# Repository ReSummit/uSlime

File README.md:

<div></div>

Micro form of SlimeVR trackers using BNO085 and ESP32-C6-MINI module, as small as possible

Limited to 1 sided PCB but utilizes two layer to achieve a maximal dimension of 25mm x 28mm (including the ESP32-C6-MINI module)

Also includes some test points if you wanna add idk RGB lights to it or something like that lol

## PCB Variants and Versions

Currently, v1.0.0 is the preferred PCB version and is listed in the releases. As a note, your red charge LED will always be on while the device is on. While this makes for a good indicator that your tracker is on, some may not like that the LED is always on. v1.1.0 fixes this but results in a long trace, change in pinout, and additional components needed.

**If you do not mind the always on LED, use v1.0.0 as it is less likely to result in RF issues. If you are bothered by the LED, use a 2k or higher SMD resistor value or use v1.1.0.**

On variants, there are currently three different types of main board PCBs and 2 types of supplementary modules. The first kind are listed as follows:
* uSlime_PCB: The default PCB with the BNO085 circuit on board. Contains the working BNO085 utilizing the internal crystal (of which there is little room for an external crystal)
* uSlime_PCB_Module: Similar to the default PCB; however, the BNO085 is replaced with a 5 pin I2C pin for attaching a uSlime_BNO085_Module on the back or front side of the PCB (in case you want to replace the IMU with a better one).
* uSlime_PCB_Pack: The default PCB but using pack resistors to attempt the reduction of part placements by quantity. **This has not been updated to v1.0.0 yet, DO NOT USE.**

For supplementary modules, the variants are as follows:
* uSlime_BNO085_Module: The default PCB for supplementary modules. In addition to the connectors that are compatible with the original SlimeVR trackers, they also have headers that you can use to connect it to something else instead if you decide not to use it for SlimeVR. This increases the versatility of the IMU for other projects. Due to the small size, a crystal could not be placed; however, one could be placed with a slightly larger PCB size.
* uSlime_BNO085: The other PCB for supplementary modules without the header pins. This is if you are sure that you are only using this for SlimeVR. You can technically still use this for other projects like with headers, but you will likely solder on wires.

## BOM and Pre-requisites

Bill of materials (BOMs) can be found in the `bom` folder within the respective PCB folder. These are generated on a by release basis, so they may not be up to date. It is highly recommended to generate the BOM using the "`Interactive Html Bom`" plugin found in typical KiCAD repository plugins.  
**Following the BOM placements using a BOM plugin to show where components are placed is mandatory, as there is no space for reference designators on the PCB.**

In addition to this, a hot plate, solder paste, and some needle tipped tweezers are also required. Flux may also be needed to fix any bridges that pop up on the board. Obviously, the components on the BOM are also required.

## Building the PCB

When ordering the PCB, choose to place the JLC PCB indicator as a preferred spot is placed on the PCB itself (if using JLCPCB for PCB production). You should also get a stencil to put solder paste on the PCB.

**Again, following the BOM placements using a BOM plugin to show where components are placed is mandatory, as there is no space for reference designators on the PCB.**
Place solder paste on the PCB. Afterwards, follow the Interactive HTML BOM to place all the capacitors, resistors, IMU, and MCU on the PCB. When ready, you can then place this on a hot plate. Please make sure that there are no bridges on the BNO085 or the USB C connector, as these can cause issues with functionality.

## Verification (MUST READ)

<div><center>   

**Before testing and using, make sure to bridge the address bridge pads on the back of the PCB.** Verify that the board and the IMU functions by flashing the ESP32-C6 firmware first. If there is no address response, something may be wrong with the IMU (more likely to fail). Once you have verified that the IMU and MCU works, you can then solder the rest of the THT components such as the external IMU connector and battery connector.

## Firmware

The PCB currently uses a ESP32-C6 or equivalent MCU. Right now, there is a pull request to introduce this MCU into the SlimeVR ESP32 firmware located here:  
[SlimeVR ESP32-C6 Pull Request](https://github.com/SlimeVR/SlimeVR-Tracker-ESP/pull/327)

The Arduino core is technically updated but is still pending its full support to the ESP32-C6 line. Therefore, treat this as a beta firmware and subject to broken features or bugs.

## PCB Limitations

Due to the inherent nature of this PCB, there is a chance that this PCB may produce RF. We have not tested for RF emission but regardless, be careful if using this in RF restricted environments.

Also, the main PCB does not have USB voltage protection circuits! Unfortunately, we ran out of time for the release but it is plausible to add it...

In addition, due to the single-sided PCB layout, this is not technically as small as it could be. There have been countless videos that showcase the design possibly being smaller. Some resistor and SMD components can also be moved to the back due to the ease in soldering those components. However, those are slated for a v2.0.0 PCB and is not expected to be released within anytime this year.

Lastly, it is known that the charger SMD compoenent tends to heat up rather quickly while charging the battery. This shouldn't reach the melting point of solder but it is worth mentioning; perhaps a more efficient IC would be better here.

## Images:
<div></div>

## Footprints Used

Some footprints and symbols were used from other sources:
* ESP32-C6 Symbol: https://github.com/sparkfun/SparkFun_Thing_Plus_ESP32_C6
* ESP32-C6 Footprint: https://github.com/espressif/kicad-libraries
* BNO085 Footprint: Provided by Colin
* AP2112K-3.3TRG1 and MCP73831T-2ACI/OT Symbol / Footprint: From a class project :)
* MHT150RGBCT Footprint: Converted from EasyEDA
* JST ZH Pinout: Same as SlimeVR PCB :D

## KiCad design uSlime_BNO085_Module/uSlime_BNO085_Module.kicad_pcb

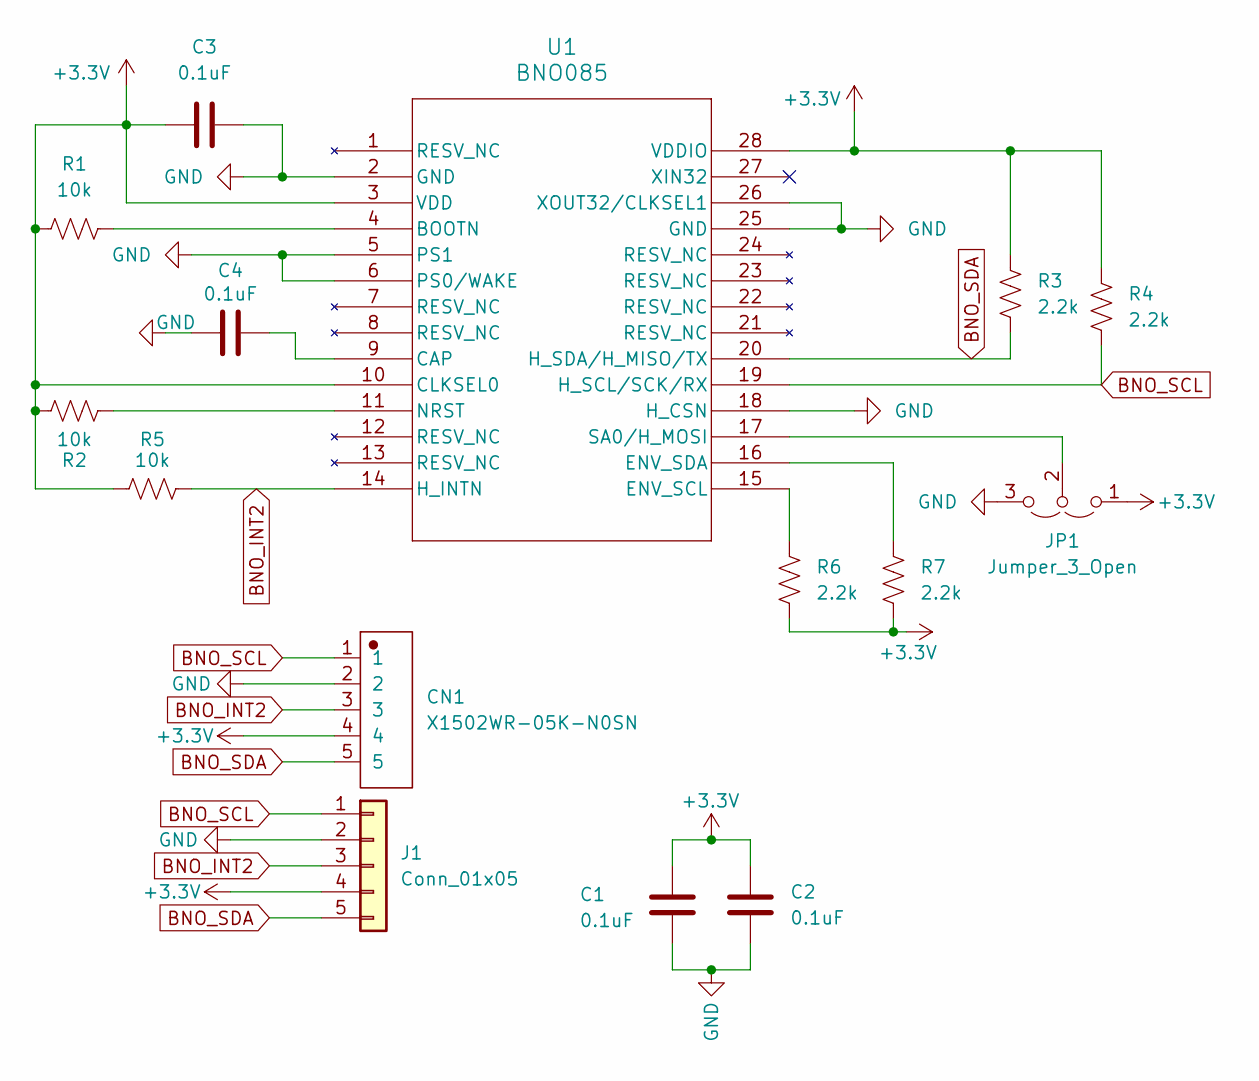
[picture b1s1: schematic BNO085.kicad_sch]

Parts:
C1, C2, C3, C4: 0.1uF; C_0402_1005Metric
CN1: X1502WR-05K-N0SN; CONN-TH_5P-P1.50_X1502WR-05K-N0SN
J1: Conn_01x05; PinHeader_1x05_P2.54mm_Vertical
JP1: Jumper_3_Open; SolderJumper-3_P1.3mm_Open_RoundedPad1.0x1.5mm
R1, R2, R5: 10k; R_0402_1005Metric
R3, R4, R6, R7: 2.2k; R_0402_1005Metric
U1: BNO085; BNO080

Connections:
+3.3V: C1.2, C2.2, C3.1, CN1.4, J1.4, JP1.1 (A), R1.1, R2.2, R3.1, R4.1, R5.1, R6.2, R7.2, U1.3 (VDD), U1.10 (CLKSEL0), U1.28 (VDDIO)
BNO_INT2: CN1.3, J1.3, R5.2, U1.14 (H_INTN)
BNO_SCL: CN1.1, J1.1, R4.2, U1.19 (H_SCL/SCK/RX)
BNO_SDA: CN1.5, J1.5, R3.2, U1.20 (H_SDA/H_MISO/TX)
GND: C1.1, C2.1, C3.2, C4.1, CN1.2, J1.2, JP1.3 (B), U1.2 (GND), U1.5 (PS1), U1.6 (PS0/WAKE), U1.18 (H_CSN), U1.25 (GND), U1.26 (XOUT32/CLKSEL1)
unnamed: JP1.2 (C), U1.17 (SA0/H_MOSI)
unnamed: R1.2, U1.4 (BOOTN)
unnamed: C4.2, U1.9 (CAP)
unnamed: R6.1, U1.15 (ENV_SCL)
unnamed: R7.1, U1.16 (ENV_SDA)
unnamed: R2.1, U1.11 (NRST)

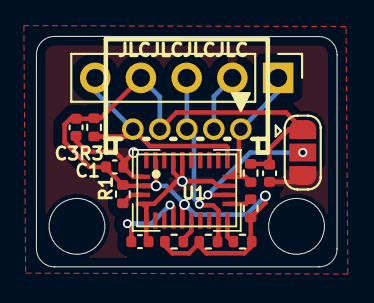
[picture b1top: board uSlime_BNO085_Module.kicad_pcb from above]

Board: 2 copper layers, 16.7 x 12.8 mm, 15 parts (0 on the bottom side), 11 nets.

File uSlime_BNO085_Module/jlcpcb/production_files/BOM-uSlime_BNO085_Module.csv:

Comment,Designator,Footprint,LCSC,Quantity
0.1uF,"C1,C2,C3,C4",C_0402_1005Metric,C141382,4
10k,"R1,R2,R5",R_0402_1005Metric,C25744,3
2.2k,"R3,R4,R6,R7",R_0402_1005Metric,C25879,4
X1502WR-05K-N0SN,CN1,CONN-TH_5P-P1.50_X1502WR-05K-N0SN,C561537,1
Conn_01x05,J1,PinHeader_1x05_P2.54mm_Vertical,,1
BNO085,U1,BNO080,,1

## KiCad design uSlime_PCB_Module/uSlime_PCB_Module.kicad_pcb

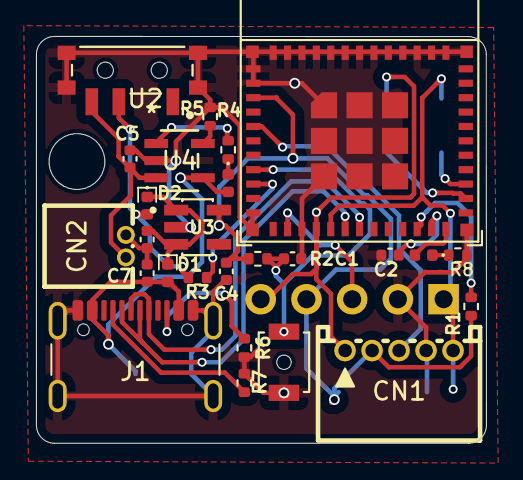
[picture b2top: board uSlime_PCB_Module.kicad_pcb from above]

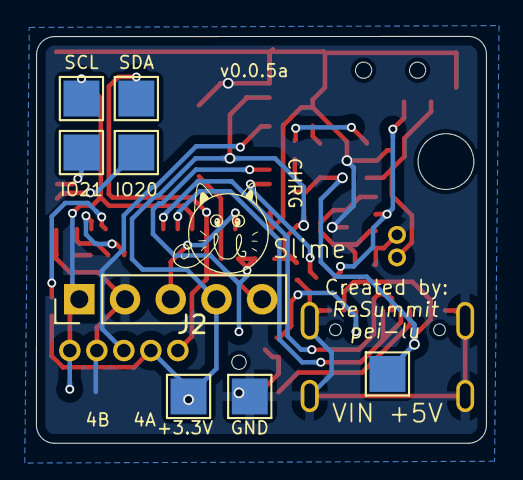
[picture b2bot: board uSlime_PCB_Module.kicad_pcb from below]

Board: 2 copper layers, 25.0 x 22.6 mm, 34 parts (8 on the bottom side), 25 nets.

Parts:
C1, C2: 0.1uF; C_0402_1005Metric
C3, C4: 10uF; C_0402_1005Metric
C5, C7: 10μF; C_0402_1005Metric
CHRG1: LED; LED_0402_1005Metric
CN1: X1502WR-05K-N0SN; CONN-TH_5P-P1.50_X1502WR-05K-N0SN
CN2: 1.25T-2AW; CONN-TH_2P-P1.25_1.25T-2AW
D1, D2: D; D_0402_1005Metric
J1: USB_C_Receptacle_USB2.0_14P; USB_C_Receptacle_GCT_USB4105-xx-A_16P_TopMnt_Horizontal
J2: Conn_01x05; PinHeader_1x05_P2.54mm_Vertical
R1, R2: 100k; R_0402_1005Metric
R3: 180k; R_0402_1005Metric
R4, R8: 1k; R_0402_1005Metric
R5: 2k; R_0402_1005Metric
R6, R7: 5.1k; R_0402_1005Metric
RESET1: SW_Push; SW_SPST_B3U-1000P-B
STAT1: LED; LED_0402_1005Metric
TP1: SDA; TestPoint_Pad_2.0x2.0mm
TP2: SCL; TestPoint_Pad_2.0x2.0mm
TP3, TP4: IO14; TestPoint_Pad_2.0x2.0mm
TP5: 3.3V; TestPoint_Pad_2.0x2.0mm
TP6: GND; TestPoint_Pad_2.0x2.0mm
TP7: VBUS; TestPoint_Pad_2.0x2.0mm
U1: ESP32-C6-MINI-1
U2: MSK-12C02_SMD_SPDT_SWITCH; SW_PCM12SMTR
U3: AP2112K-3.3TRG1; SOT95P285X140-5N
U4: MCP73831T-2ACI/OT; SOT-23-5_MC_MCH

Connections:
+3.3V: C4.1, CN1.2, J2.4, R1.2, R2.2, TP5.1, U1.3 (3V3), U3.5 (VOUT)
/ESP32-C6FH4/ESP_EN: C1.1, R2.1, RESET1.2, U1.8 (EN)
/ESP32-C6FH4/IO8: R1.1, U1.22 (IO8)
/ESP32-C6FH4/IO9/BOOT: C2.1, U1.23 (IO9)
/ESP32-C6FH4/IO18/~CS: STAT1.2 (A), U1.24 (SDIO_CMD/IO18)
/ESP32-C6FH4/IO20/PICO: TP3.1, U1.26 (SDIO_D0/IO20)
/ESP32-C6FH4/IO21/POCI: TP4.1, U1.27 (SDIO_D1/IO21)
BNO_INT: J2.3, U1.13 (XTAL_32K_N/IO1)
BNO_INT2: CN1.3, U1.5 (IO2)
BNO_SCL: CN1.5, J2.1, TP2.1, U1.16 (MTDO/LP_SCL/IO7)
BNO_SDA: CN1.1, J2.5, TP1.1, U1.15 (MTCK/LP_SDA/IO6)
BatSense: R3.2, U1.9 (MTMS/LP_RX/IO4)
D+ P: J1.A6 (D+), J1.B6 (D+), U1.18 (USB_D+/IO13)
D- N: J1.A7 (D-), J1.B7 (D-), U1.17 (USB_D-/IO12)
GND: C1.2, C2.2, C3.2, C4.2, C5.2, C7.2, CN1.4, CN2.1, J1.A1 (GND), J1.A12 (GND), J1.B1 (GND), J1.B12 (GND), J1.S1 (SHIELD), J2.2, R5.2, R6.1, R7.1, R8.1, RESET1.1, TP6.1, U1.1 (GND), U1.2 (GND), U1.11 (GND), U1.14 (GND), U1.36 (GND), U1.37 (GND), U1.38 (GND), U1.39 (GND), U1.40 (GND), U1.41 (GND), U1.42 (GND), U1.43 (GND), U1.44 (GND), U1.45 (GND), U1.46 (GND), U1.47 (GND), U1.48 (GND), U1.49 (GND), U1.50 (GND), U1.51 (GND), U1.52 (GND), U1.53 (GND), U2.GND, U3.2 (GND), U4.2 (VSS)
unnamed: CHRG1.1 (K), R4.1
unnamed: C3.1, D1.1 (K), D2.1 (K), U3.1 (VIN), U3.3 (EN)
unnamed: D2.2 (A), R3.1, U2.COM
unnamed: J1.A5 (CC1), R7.2
unnamed: J1.B5 (CC2), R6.2
unnamed: R8.2, STAT1.1 (K)
unnamed: R5.1, U4.5 (PROG)
unnamed: R4.2, U4.1 (STAT)
VBAT: C5.1, CN2.2, U2.L1, U4.3 (VBAT)
VBUS: C7.1, CHRG1.2 (A), D1.2 (A), J1.A4 (VBUS), J1.A9 (VBUS), J1.B4 (VBUS), J1.B9 (VBUS), TP7.1, U4.4 (VDD)

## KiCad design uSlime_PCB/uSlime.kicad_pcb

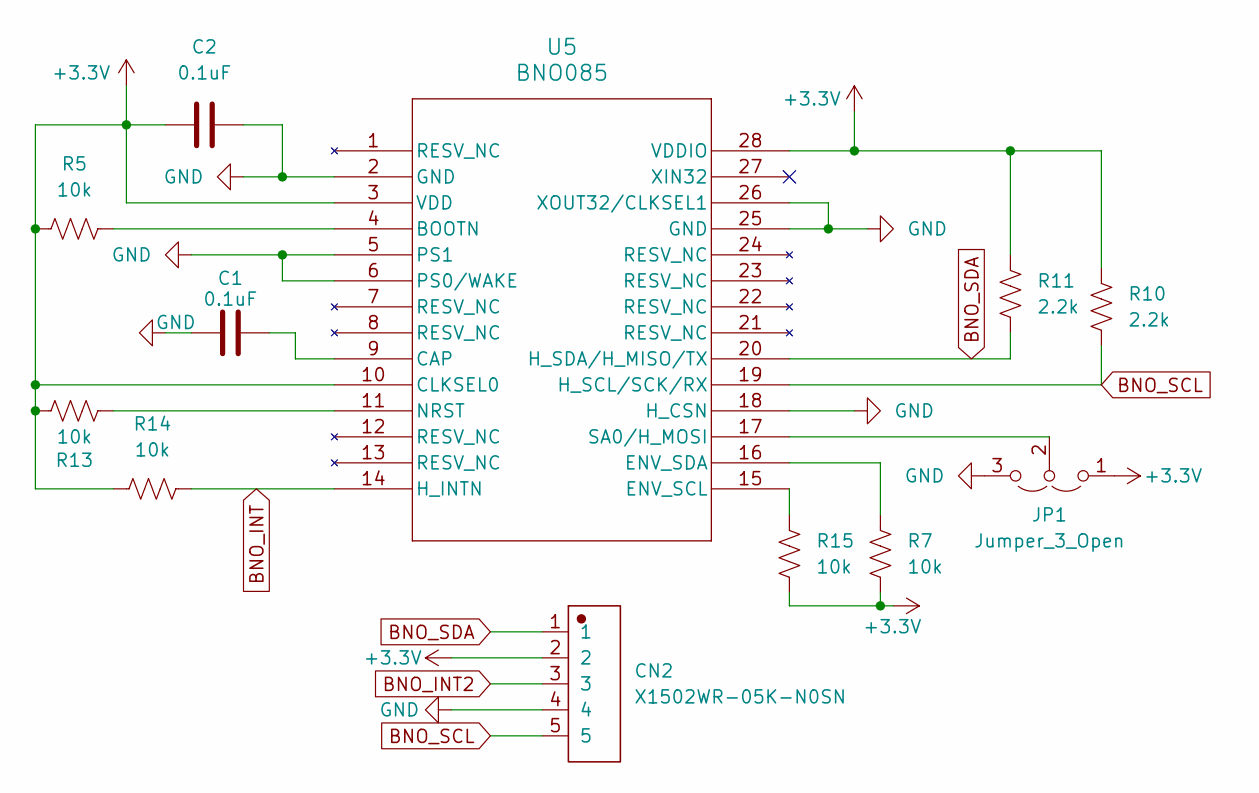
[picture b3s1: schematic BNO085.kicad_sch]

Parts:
C1, C2: 0.1uF; C_0402_1005Metric
CN2: X1502WR-05K-N0SN; CONN-TH_5P-P1.50_X1502WR-05K-N0SN
JP1: Jumper_3_Open; SolderJumper-3_P1.3mm_Open_RoundedPad1.0x1.5mm
R5, R7, R13, R14, R15: 10k; R_0402_1005Metric
R10, R11: 2.2k; R_0402_1005Metric
U5: BNO085; BNO080

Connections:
+3.3V: C2.1, CN2.2, JP1.1 (A), R5.1, R7.2, R10.1, R11.1, R13.2, R14.1, R15.2, U5.3 (VDD), U5.10 (CLKSEL0), U5.28 (VDDIO); also elsewhere on the board
BNO_INT: R14.2, U5.14 (H_INTN); also elsewhere on the board
BNO_INT2: CN2.3; also elsewhere on the board
BNO_SCL: CN2.5, R10.2, U5.19 (H_SCL/SCK/RX); also elsewhere on the board
BNO_SDA: CN2.1, R11.2, U5.20 (H_SDA/H_MISO/TX); also elsewhere on the board
GND: C1.1, C2.2, CN2.4, JP1.3 (B), U5.2 (GND), U5.5 (PS1), U5.6 (PS0/WAKE), U5.18 (H_CSN), U5.25 (GND), U5.26 (XOUT32/CLKSEL1); also elsewhere on the board
unnamed: JP1.2 (C), U5.17 (SA0/H_MOSI)
unnamed: R5.2, U5.4 (BOOTN)
unnamed: C1.2, U5.9 (CAP)
unnamed: R15.1, U5.15 (ENV_SCL)
unnamed: R7.1, U5.16 (ENV_SDA)
unnamed: R13.1, U5.11 (NRST)

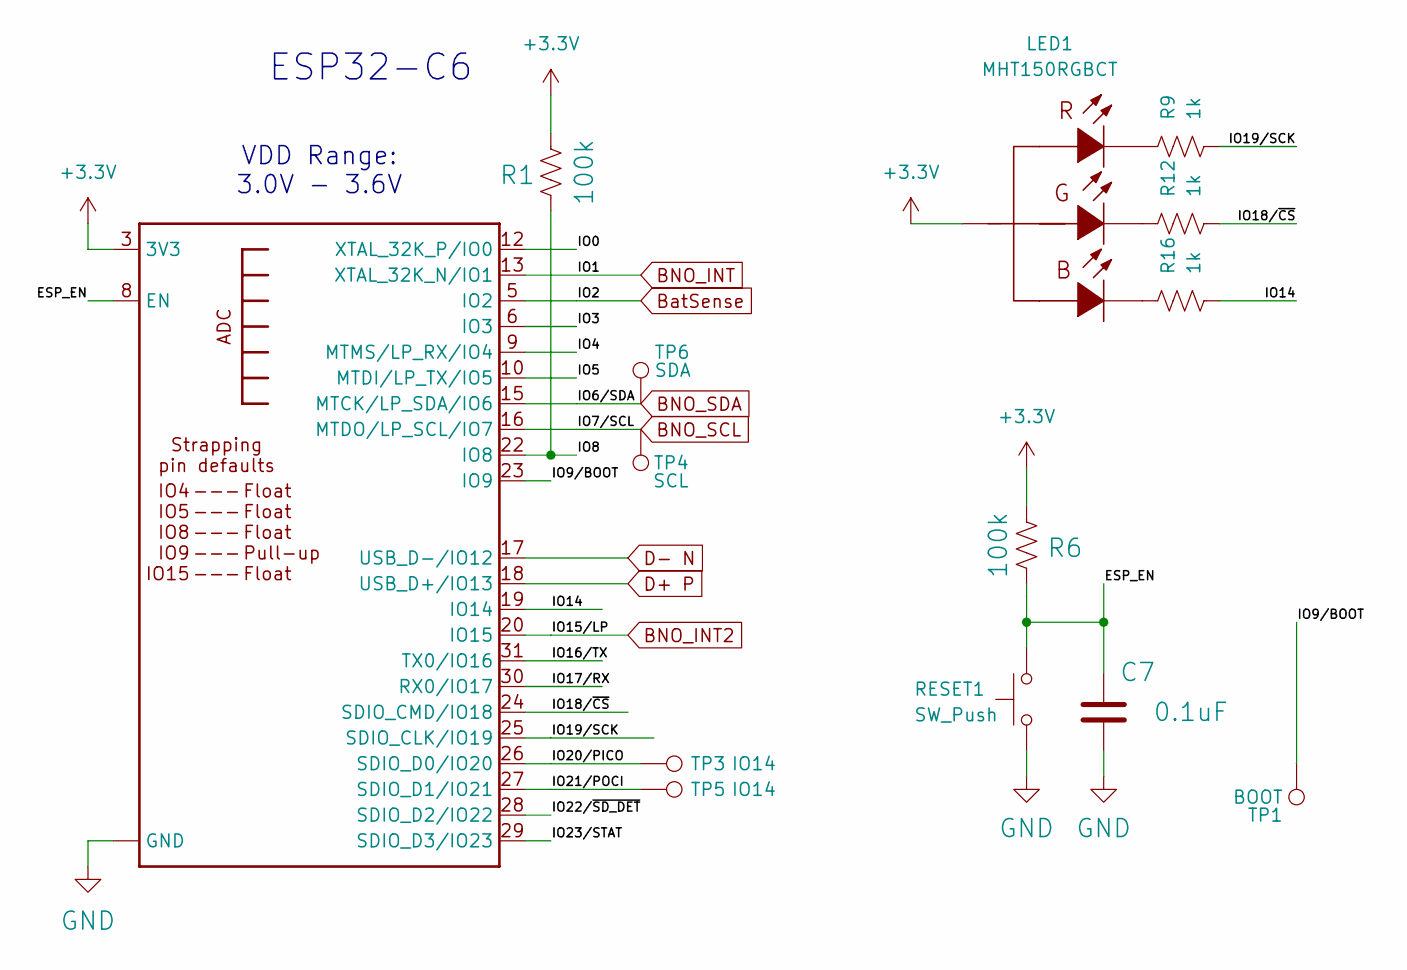
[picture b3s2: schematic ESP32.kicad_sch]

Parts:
C7: 0.1uF; C_0402_1005Metric
LED1: MHT150RGBCT; LED-ARRAY-SMD_1206-4P-L3.2-W1.3-BR-EH
R1, R6: 100k; R_0402_1005Metric
R9, R12, R16: 1k; R_0402_1005Metric
RESET1: SW_Push; SW_SPST_B3U-1000P-B
TP1: BOOT; TestPoint_Pad_D1.0mm
TP3, TP5: IO14; TestPoint_Pad_2.0x2.0mm
TP4: SCL; TestPoint_Pad_2.0x2.0mm
TP6: SDA; TestPoint_Pad_2.0x2.0mm
U4: ESP32-C6-MINI-1

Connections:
+3.3V: LED1.1 (+), R1.2, R6.2, U4.3 (3V3); also elsewhere on the board
/ESP32-C6FH4/ESP_EN: C7.1, R6.1, RESET1.2, U4.8 (EN)
/ESP32-C6FH4/IO0: U4.12 (XTAL_32K_P/IO0)
/ESP32-C6FH4/IO3: U4.6 (IO3)
/ESP32-C6FH4/IO4: U4.9 (MTMS/LP_RX/IO4)
/ESP32-C6FH4/IO5: U4.10 (MTDI/LP_TX/IO5)
/ESP32-C6FH4/IO8: R1.1, U4.22 (IO8)
/ESP32-C6FH4/IO14: R16.1, U4.19 (IO14)
/ESP32-C6FH4/IO16/TX: U4.31 (TX0/IO16)
/ESP32-C6FH4/IO17/RX: U4.30 (RX0/IO17)
/ESP32-C6FH4/IO18/~CS: R12.1, U4.24 (SDIO_CMD/IO18)
/ESP32-C6FH4/IO19/SCK: R9.1, U4.25 (SDIO_CLK/IO19)
/ESP32-C6FH4/IO20/PICO: TP3.1, U4.26 (SDIO_D0/IO20)
/ESP32-C6FH4/IO21/POCI: TP5.1, U4.27 (SDIO_D1/IO21)
/ESP32-C6FH4/IO22/~SD_DET: U4.28 (SDIO_D2/IO22)
/ESP32-C6FH4/IO23/STAT: U4.29 (SDIO_D3/IO23)
BNO_INT: U4.13 (XTAL_32K_N/IO1); also elsewhere on the board
BNO_INT2: U4.20 (IO15); also elsewhere on the board
BNO_SCL: TP4.1, U4.16 (MTDO/LP_SCL/IO7); also elsewhere on the board
BNO_SDA: TP6.1, U4.15 (MTCK/LP_SDA/IO6); also elsewhere on the board
BatSense: U4.5 (IO2); also elsewhere on the board
D+ P: U4.18 (USB_D+/IO13); also elsewhere on the board
D- N: U4.17 (USB_D-/IO12); also elsewhere on the board
GND: C7.2, RESET1.1, U4.1 (GND), U4.2 (GND), U4.11 (GND), U4.14 (GND), U4.36 (GND), U4.37 (GND), U4.38 (GND), U4.39 (GND), U4.40 (GND), U4.41 (GND), U4.42 (GND), U4.43 (GND), U4.44 (GND), U4.45 (GND), U4.46 (GND), U4.47 (GND), U4.48 (GND), U4.49 (GND), U4.50 (GND), U4.51 (GND), U4.52 (GND), U4.53 (GND); also elsewhere on the board
unnamed: LED1.2 (-), R16.2
unnamed: LED1.3 (-), R12.2
unnamed: LED1.4 (-), R9.2

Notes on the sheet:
ESP32-C6
VDD Range: 3.0V - 3.6V

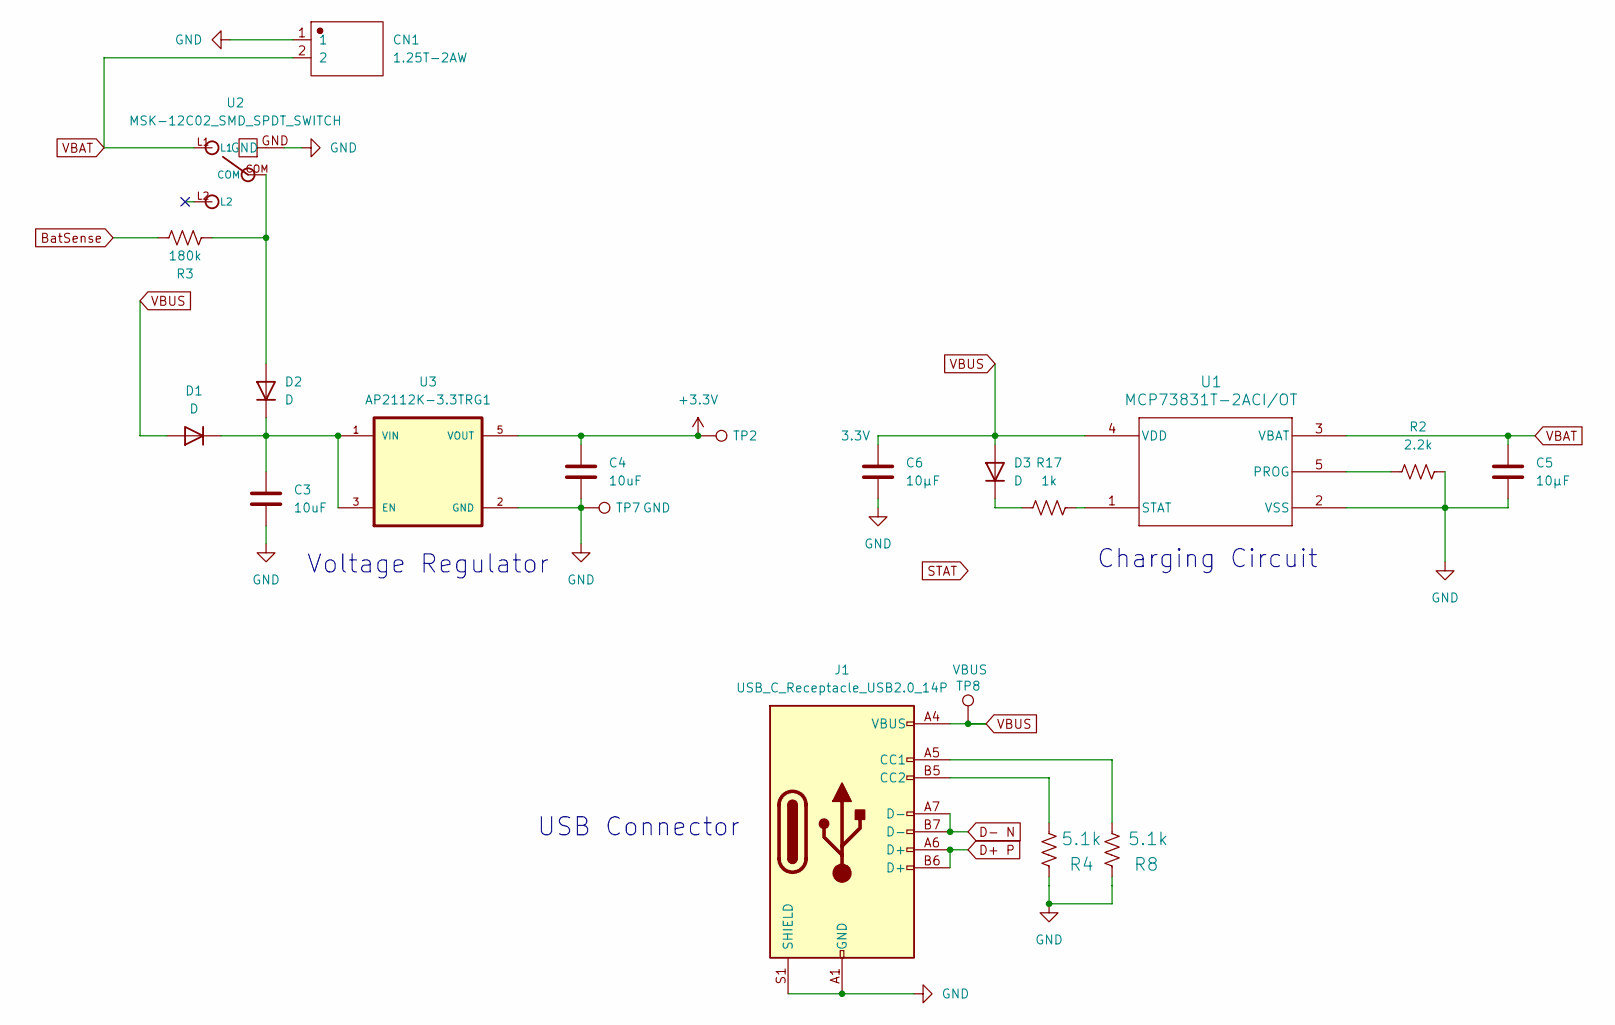
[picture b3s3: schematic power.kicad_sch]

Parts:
C3, C4: 10uF; C_0402_1005Metric
C5, C6: 10μF; C_0402_1005Metric
CN1: 1.25T-2AW; CONN-TH_2P-P1.25_1.25T-2AW
D1, D2: D; D_0402_1005Metric
D3: D; D_0603_1608Metric
J1: USB_C_Receptacle_USB2.0_14P; USB_C_Receptacle_GCT_USB4105-xx-A_16P_TopMnt_Horizontal
R2: 2.2k; R_0402_1005Metric
R3: 180k; R_0402_1005Metric
R4, R8: 5.1k; R_0402_1005Metric
R17: 1k; R_0402_1005Metric
TP2: 3.3V; TestPoint_Pad_2.0x2.0mm
TP7: GND; TestPoint_Pad_2.0x2.0mm
TP8: VBUS; TestPoint_Pad_2.0x2.0mm
U1: MCP73831T-2ACI/OT; SOT-23-5_MC_MCH
U2: MSK-12C02_SMD_SPDT_SWITCH; SW_PCM12SMTR
U3: AP2112K-3.3TRG1; SOT95P285X140-5N; PARTREV 2-2

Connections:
+3.3V: C4.1, TP2.1, U3.5 (VOUT); also elsewhere on the board
BatSense: R3.2; also elsewhere on the board
D+ P: J1.A6 (D+), J1.B6 (D+); also elsewhere on the board
D- N: J1.A7 (D-), J1.B7 (D-); also elsewhere on the board
GND: C3.2, C4.2, C5.2, C6.2, CN1.1, J1.A1 (GND), J1.A12 (GND), J1.B1 (GND), J1.B12 (GND), J1.S1 (SHIELD), R2.2, R4.1, R8.1, TP7.1, U1.2 (VSS), U2.GND, U3.2 (GND); also elsewhere on the board
unnamed: C3.1, D1.1 (K), D2.1 (K), U3.1 (VIN), U3.3 (EN)
unnamed: D2.2 (A), R3.1, U2.COM
unnamed: D3.1 (K), R17.1
unnamed: J1.A5 (CC1), R8.2
unnamed: J1.B5 (CC2), R4.2
unnamed: R2.1, U1.5 (PROG)
unnamed: R17.2, U1.1 (STAT)
VBAT: C5.1, CN1.2, U1.3 (VBAT), U2.L1
VBUS: C6.1, D1.2 (A), D3.2 (A), J1.A4 (VBUS), J1.A9 (VBUS), J1.B4 (VBUS), J1.B9 (VBUS), TP8.1, U1.4 (VDD)

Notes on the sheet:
Charging Circuit
Voltage Regulator
USB Connector

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
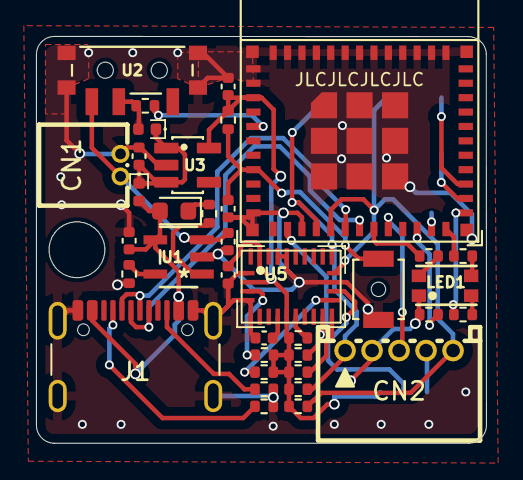
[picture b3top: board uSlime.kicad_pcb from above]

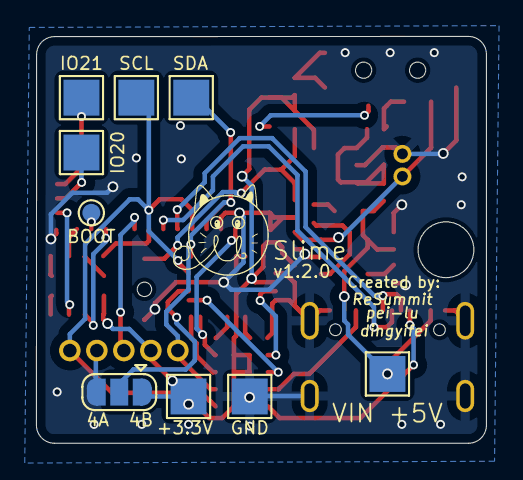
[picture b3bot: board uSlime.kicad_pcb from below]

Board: 2 copper layers, 25.0 x 22.6 mm, 46 parts (9 on the bottom side), 35 nets.

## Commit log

2024-05-10 Init Kicad
2024-05-10 Accidental move of readme and license
2024-05-10 Add hierarchy for power and ESP32
2024-05-17 Insert ESP32-C6FH4
2024-05-17 add power circuit
2024-05-17 library update
2024-05-17 Make sym look nicer
2024-05-17 updatepower
2024-05-17 Update schematic and libraries
2024-05-17 Update footprints
2024-05-21 Modify ESP32
2024-05-21 1st attempt finish BNO085
2024-05-21 Update PCB
2024-05-22 update power supply
2024-05-23 Add switches, change PCB
2024-05-24 update power
2024-05-26 Modify ESP32 connections
2024-05-26 Recover old power schematic
2024-05-26 Replace ESP32 symbol with right ESP32
2024-05-26 Condense schematic
2024-05-26 PCB Smol Time
2024-05-26 Cleanup extra files
2024-05-26 Add connector for testing
2024-05-26 Add fiducial
2024-05-27 update power circuit
2024-05-27 update battery sense
2024-05-27 Create prelim PCB
2024-05-27 Add status LED
2024-05-28 2nd version but smaller at 25x28
2024-05-28 Fix some DRC and generate gerber
    Some errors popped up on annular diameter, fixed and generated gerber
    files for production
2024-05-28 Add some jlcpcb BOM info and zip
2024-05-29 Add logo and remove crystal
2024-05-29 Rearrange capacitor silkscreen
2024-06-03 Add NC points
2024-06-03 Add prelim BOM
2024-06-05 Revamp pwr resistor, cap placement, fix switch sym
    Fix placement of resistors and capacitor placement b/c additional
    components were added to power circuit and weren't correct...
    Also fixed switch symbol so wires actually connect to it in schematic
2024-06-05 Add gerber zip
2024-06-06 Add BNO085 PCB, restructure folders
2024-06-06 Fix weird submodule reference
2024-06-06 Restructure gbr exports, add to README
2024-06-06 Add pics and logo
2024-06-06 Ah em wanna fix README format
2024-07-13 backup sync
2024-07-25 Faulty BNO085 footprint
    First, I do not like you UltraLibrarian anymore, for you have wasted a
    lot of time and effort (and money) on footprints that are just straight
    up wrong. I am this close to unleashing unbridled rage on this but will
    bottle it up for now.
    Second, I took the BNO085 footprint from the official SlimeVR tracker
    and put it in this project. At least they have the right footprint...
2024-07-25 Add version number v0.0.1a
2024-08-09 update selection i2c
2024-08-11 update schmetic
    fix pull up
2024-08-11 Update main board BNO
2024-08-11 backup
2024-08-13 Update main PCB schematic
2024-08-14 v0.0.2a Modify BNO I2C
2024-08-17 update gbr file
2024-08-22 v0.0.3a Fix wrong I2C address for 0x4A
2024-08-22 Clean up extra files
2024-08-23 Change bat sense pin to not IO0
2024-08-27 gerberupdate
2024-08-30 Fix BNO wrong pin order
2024-09-20 Connect DI without resistor
2024-09-20 v0.0.4a
2024-09-20 Add models for SMD, STEP of PCB
2024-10-20 v0.0.5: Invert CLKSEL pin to 3.3V
2024-10-21 Add module version
2024-10-22 Connect pin 26 to GND
2024-10-22 Add dingyifei to PCB ref
2024-10-23 update schmetic
2024-10-24 Modify PCB to add resistors to pins 14, 15, 16
2024-10-24 backups
2024-10-25 Consolidate libs
2024-11-03 Push pack resistor variant
2024-11-03 v1.0.0 - Use 1206 LED, add resistor pack suggestion
2024-11-03 Remove GPIO9 capacitor causing boot problems
2024-11-08 Add JLCPCB associated parts
2024-11-08 Export mainboard PCB for JLC ident placement
2024-11-16 Change charge LED to 2.2k, always on light if not charging
2024-11-16 v1.1.0 - Add 603 LED and resistor for charger status
2024-11-16 Forgot to change silkscreen positions
2024-11-18 v1.2.0 - Refactor component placement and electrical accuracy
2024-11-21 Add docs to README
2024-11-21 Add footprint sources
2025-01-06 Clarify LICENSE, accidental placement in folders
